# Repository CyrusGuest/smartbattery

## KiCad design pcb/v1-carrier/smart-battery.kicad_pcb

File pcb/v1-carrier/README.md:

# Smart Battery PCB

KiCad project for the Smart Battery carrier PCB. The board is a **carrier** that off-the-shelf modules plug into via pin headers — no bare ICs in v1.

> **Source of truth for connections**: `firmware/HARDWARE.md` in the repo root. Anything here that contradicts that file is wrong; HARDWARE.md wins.

## First-time KiCad setup

1. **Open KiCad** (`/Applications/KiCad/KiCad.app`).
2. KiCad will ask whether to import settings from a previous version — pick **"Start with default settings"**.
3. KiCad will ask about library paths — accept the defaults.
4. **File → New Project…** → navigate to `~/programming/smart-battery/pcb/` → name it `smart-battery` → uncheck "Create a new folder" (we already have one) → save.
5. You should now see `smart-battery.kicad_pro` and `smart-battery.kicad_sch` in this directory.

That's it for setup. Now we draw the schematic.

## Schematic plan

This translates `firmware/HARDWARE.md` into KiCad symbols and nets. **Read HARDWARE.md first** to understand the topology — especially the INA219 in-line-with-cell+ wiring.

### Symbols to place

You won't find ready-made symbols for module breakouts in KiCad's stock library. For a carrier PCB, the right move is to use generic **pin header** symbols (`Connector_Generic:Conn_01x06`, etc.) and label them with the module name.

| Symbol                       | Module it represents                | Pin count | KiCad symbol                        |
| ---------------------------- | ----------------------------------- | --------- | ----------------------------------- |
| **U1 — ESP32**               | ESP32 dev board (whichever you have) | varies (15, 19, or 20 per side) | `Connector_Generic:Conn_02x15_Odd_Even` (or matching count) |
| **U2 — INA219 breakout**     | Adafruit/clone INA219               | 6         | `Connector_Generic:Conn_01x06`      |
| **U3 — TP4056 USB-C charger**| TP4056 module                       | 4–6 (varies) | `Connector_Generic:Conn_01x05` or `01x06` depending on module |
| **U4 — SSD1306 OLED (SPI)**  | 128×64 SPI OLED                     | 7         | `Connector_Generic:Conn_01x07`      |
| **U5 — MOSFET**              | Logic-level N-channel               | 3 (G/D/S) | `Device:Q_NMOS_GSD` (real symbol, not header) |
| **SW1 — Fire switch**        | Momentary, normally-open            | 2         | `Switch:SW_Push`                    |
| **J1 — Coil connector**      | Whatever you pick (510 thread / pads / connector) | 2 | `Connector_Generic:Conn_01x02` |
| **BT1 — LiPo cell**          | Single cell via JST-PH              | 2         | `Connector:Conn_01x02_Pin` (label as JST-PH) |

> Why headers? Because in v1 you're soldering pin headers onto each module and onto the carrier PCB. The "symbol" is just the row of holes the module plugs into. Footprint matches.

### Nets (connections)

Pulled straight from `firmware/HARDWARE.md`. **Power topology is critical** — the INA219 sits in series with the cell+, so loads connect to V−, NOT V+.

**Power rail (the high-current path)**

```
BT1 (cell)   ─[+]─▶ U2.V+ (INA219)
                    │
                    [internal shunt]
                    │
                   U2.V- ──┬──▶ U3.OUT+ (TP4056 BAT+ side, charger output to "system")
                            ├──▶ U1.VIN  (ESP32 dev board VIN)
                            ├──▶ U5.D    (MOSFET drain)
                            └──▶ J1.1    (coil + terminal — the OTHER side goes to U5.S)

BT1 (cell)   ─[−]─▶ GND  ───┬── U2.GND, U3.GND, U1.GND, J1.2, etc.
U3 USB-C input ─── (handled internally by the TP4056 module)
```

Then `U5.G` (MOSFET gate) is driven by `U1.GPIO27`, and `U5.S` (source) returns to GND through the coil. So the coil is between **V−rail** and the **MOSFET drain**, with the source on GND. (Standard low-side switch.)

**3.3 V rail (logic)**

```
U1 (ESP32) 3V3 pin ──┬── U2.Vcc (INA219 logic supply, 3.3V — NOT cell rail)
                      └── U4.VCC (OLED)
```

**I²C (INA219)**

```
U1.GPIO21 ── U2.SDA
U1.GPIO22 ── U2.SCL
```

(Optional but recommended: 4.7 kΩ pull-ups from SDA → 3V3 and SCL → 3V3. The Adafruit INA219 breakout already has them — if you're using one, skip.)

**SPI (OLED)**

```
U1.GPIO5  ── U4.CS
U1.GPIO17 ── U4.DC
U1.GPIO16 ── U4.RST
U1.GPIO23 ── U4.MOSI  (labelled "D1" or "SDA" on some OLED boards)
U1.GPIO18 ── U4.CLK   (labelled "D0" or "SCL" on some OLED boards)
```

**Fire switch**

```
U1.GPIO4 ── SW1.1
SW1.2 ──── GND
```

(Internal pull-up on GPIO 4 is enabled in firmware — no external resistor needed.)

**MOSFET gate**

```
U1.GPIO27 ──[Rg, ~220 Ω]── U5.G
                            │
                           [Rgs, 100 kΩ to GND]   <-- pull-down so the gate is OFF
                            │                          before ESP32 boots / on reset
                            ▼
                           GND
```

This is belt-and-suspenders with the firmware's `digitalWrite(27, LOW)` first thing in `setup()`. The pull-down keeps the MOSFET off during the few ms before the ESP32 even reaches `setup()`.

## Workflow checklist

Each step has a finish line — when you can check the box, move on.

- [ ] **Project created** — `pcb/smart-battery.kicad_pro` exists.
- [ ] **Schematic drawn** — open `smart-battery.kicad_sch`, place all symbols above, wire them per the nets above. Use net labels (the green `<` arrow tool) for power rails (`+BATT_V+`, `+SYS`, `+3V3`, `GND`) — they're cleaner than running long wires.
- [ ] **ERC pass** — Inspect → Electrical Rules Checker → Run. Should be 0 errors. (Warnings about no-connect on unused header pins are fine.)
- [ ] **Footprints assigned** — Tools → Assign Footprints. For headers use `Connector_PinHeader_2.54mm:PinHeader_1x{N}_P2.54mm_Vertical`. For the MOSFET, pick `Package_TO_SOT_SMD:SOT-23` (assuming surface-mount) or `Package_TO_SOT_THT:TO-220-3_Vertical` (through-hole).
- [ ] **PCB layout** — File → Switch to PCB Editor. Update from schematic (the green ↓ arrow). Place modules. Route. Run DRC.
- [ ] **Manufacturing files** — once happy, File → Fabrication Outputs → Gerbers (and drill files). Send to JLCPCB / PCBWay / OSH Park.

## Tips for first-time PCB layout

- **Set a board outline first** before placing parts. Edit the `Edge.Cuts` layer with a rectangle (your Geekbar form factor — see chat with Claude for current target dimensions).
- **Place mechanical parts first**: USB-C jack on one short edge, fire switch on a long edge, OLED in the center, coil connector on the opposite short edge.
- **Power traces wider than signal**: 1.0–2.0 mm for the cell/coil rail (carries amps), 0.25 mm is fine for I²C / SPI / GPIO.
- **Keep INA219 close to the cell connector** — its sense path is part of the high-current loop, and any wire between the cell and INA V+ is shunt resistance you didn't measure.
- **DRC must be clean** before exporting gerbers. Always.

## When you're stuck

`HARDWARE.md` and this README cover *what* to wire. If KiCad UI is the question, check:

- KiCad's built-in "Getting Started in KiCad" tutorial: Help → Getting Started.
- Digi-Key's KiCad video series on YouTube — short, current, and free.
- Or just ask Claude — paste the saved `.kicad_sch` / `.kicad_pcb` content (they're plain-text S-expressions) and I can read and suggest changes.

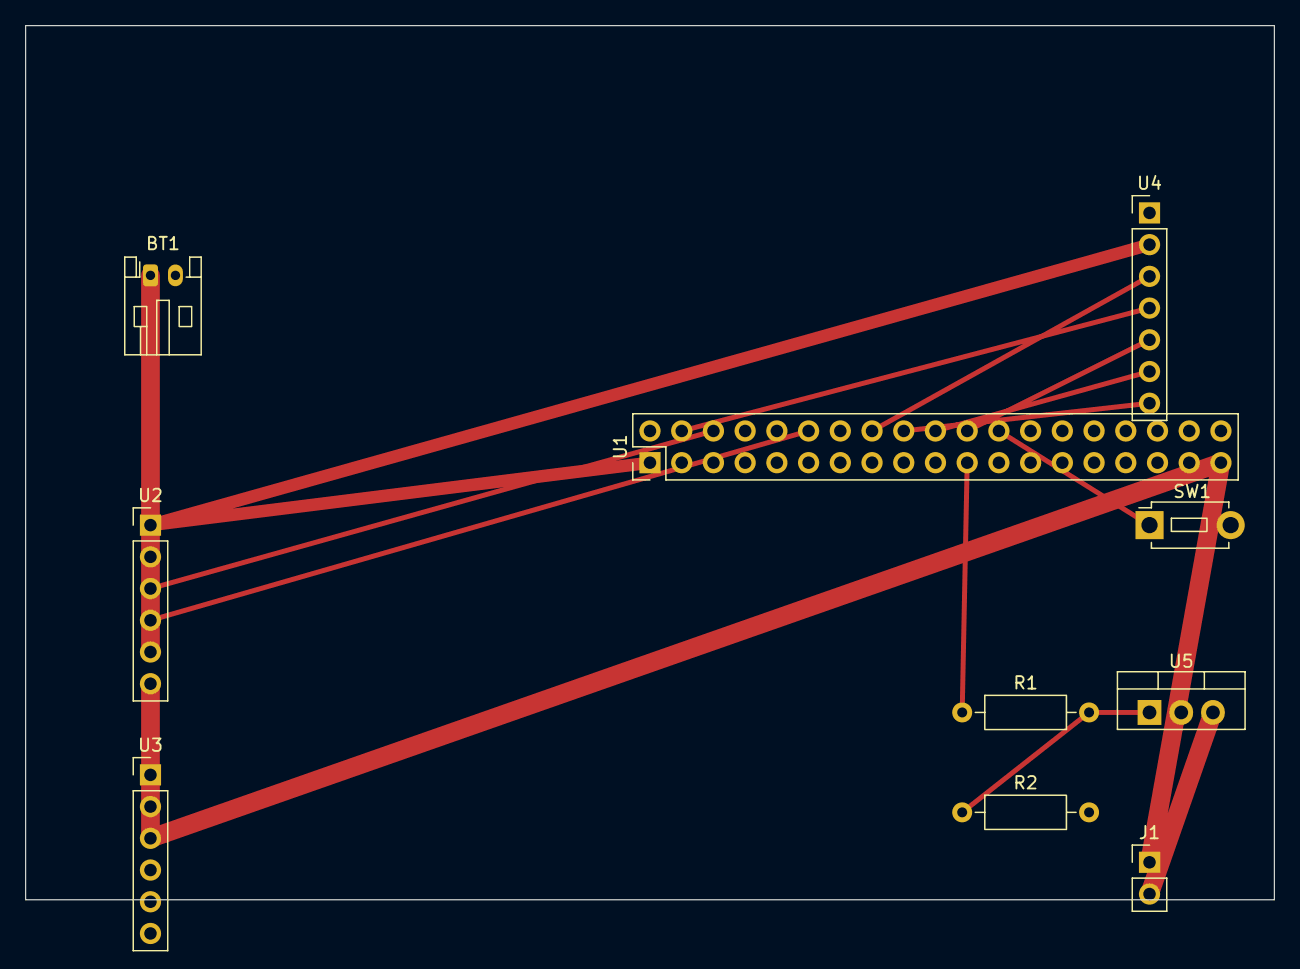
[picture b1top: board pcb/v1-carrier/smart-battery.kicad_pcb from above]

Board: 2 copper layers, 100.0 x 70.0 mm, 10 parts (0 on the bottom side), 15 nets.

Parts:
BT1: LiPo 1S; JST_PH_S2B-PH-K_1x02_P2.00mm_Horizontal
J1: Coil; PinHeader_1x02_P2.54mm_Vertical
R1: 220; R_Axial_DIN0207_L6.3mm_D2.5mm_P10.16mm_Horizontal
R2: 100k; R_Axial_DIN0207_L6.3mm_D2.5mm_P10.16mm_Horizontal
SW1: Fire; SW_PUSH_1P1T_6x3.5mm_H4.3_APEM_MJTP1243
U1: ESP32 38-pin; PinHeader_2x19_P2.54mm_Vertical
U2: INA219; PinHeader_1x06_P2.54mm_Vertical
U3: TP4056; PinHeader_1x06_P2.54mm_Vertical
U4: OLED; PinHeader_1x07_P2.54mm_Vertical
U5: N-MOSFET; TO-220-3_Vertical

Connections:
+3V3: U1.1, U2.1, U4.2
+CELL: BT1.1, U2.5
+SYS: J1.1, U1.37, U2.6, U3.1, U3.3
COIL_GATE: R1.2, R2.1, U5.1
COIL_LOW: J1.2, U5.3
COIL_PWM: R1.1, U1.21
GND: BT1.2, R2.2, SW1.2, U1.2, U1.27, U1.38, U2.2, U3.2, U3.4, U4.1, U5.2
OLED_CLK: U1.16, U4.3
OLED_CS: U1.18, U4.7
OLED_DC: U1.20, U4.6
OLED_MOSI: U1.4, U4.4
OLED_RST: U1.22, U4.5
SCL: U1.6, U2.3
SDA: U1.12, U2.4
SWITCH: SW1.1, U1.24

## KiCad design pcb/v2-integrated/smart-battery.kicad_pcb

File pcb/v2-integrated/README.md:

# Smart Battery PCB — v2 (Integrated SMD)

Production-target board: fully integrated SMD design, JLCPCB PCBA-assembled, no plug-in modules. Replaces the v1 carrier prototype at `../v1-carrier/`.

## Goals

- **Compact**: target ≤ 30 × 80 mm, fits in a Geekbar-style enclosure alongside a 1S LiPo pouch
- **Mass-producible**: every part on JLCPCB's Basic or Extended catalog, all SMD, single-side population where feasible
- **No hand-soldering**: end user receives an assembled PCBA from JLCPCB
- **USB-C flashing & charging**: single port for both, no extra programmer needed
- **Looks like a real product**: tasteful PCB silkscreen, components arranged so the housing can be a clean rectangular envelope

## Block diagram

```
USB-C ──┬──► TP4056 (charger) ──► P+ ─┬──► INA219.V- (= +SYS)
        │                             │
        │     CC1/CC2 = 5.1k pdwn     │
        ▼                             │
       ESD                            │
        │                             │
        ▼                             │
  ESP32-S3 D+/D-                      │
                                      │
Cell+ ──► INA219.V+ ──[shunt 0.1Ω]──┘
Cell− ──► FS8205A ──► (DW01A controls) ──► system GND

+SYS ──► TPS63031DSK ──► +3V3 ──► ESP32-S3, INA219_logic, OLED

ESP32-S3:
  GPIO 6  ──► R(220) ──► AO3400A gate ──┐
                          │              │
  GPIO 4 ◄── fire switch  ▼              ▼
  GPIO 5/11/16/17/18  → OLED SPI    drain ──► coil ──► J4 (510 thread)
  GPIO 8/9  → I²C ── INA219          source ─► GND     +SYS ──► coil top
  GPIO 19/20 → USB D-/D+ (native)    SS34 flyback drain↔+SYS
```

## BOM (target parts)

| Ref      | Part                     | Package        | LCSC?  | Notes |
|----------|--------------------------|----------------|--------|-------|
| U1       | ESP32-S3-MINI-1-N4       | LGA-65 module  | basic  | 4 MB flash, no PSRAM, PCB antenna |
| U2       | TP4056-42-ESOP8          | ESOP-8         | basic  | 1 A charger; PROG = 1.2 kΩ |
| U3       | DW01A                    | SOT-23-6       | basic  | Cell over-discharge / over-charge / over-current control |
| U4       | FS8205A                  | SOT-23-6       | basic  | Dual N-MOSFET for protection |
| U5       | INA219AIDR               | SOIC-8         | basic  | Bus voltage + current sense, addr 0x40 |
| U6       | TPS63031DSK              | SON-10         | extended | Buck-boost, fixed 3.3 V, ≤500 mA |
| Q1       | AO3400A                  | SOT-23         | basic  | Coil-drive N-MOSFET |
| D1       | SS34                     | SMA            | basic  | Flyback Schottky |
| D2       | USBLC6-2SC6              | SOT-23-6       | basic  | USB ESD protection |
| LED1,2   | 0603 LED green / red     | 0603           | basic  | Charge / standby indicators |
| L1       | 1.5 µH 2.2A              | 1210           | basic  | TPS63031 inductor |
| Rshunt   | 0.1 Ω 1% 1 W             | 2512           | basic  | INA219 sense (matches firmware calibration) |
| R1, R2   | 5.1 kΩ                   | 0603           | basic  | USB-C CC pull-downs (USB2-only sink) |
| Rprog    | 1.2 kΩ                   | 0603           | basic  | TP4056 charge current → 1 A |
| R_LED1,2 | 1 kΩ                     | 0603           | basic  | LED current limit |
| Rg       | 220 Ω                    | 0603           | basic  | MOSFET gate series |
| Rgs      | 100 kΩ                   | 0603           | basic  | MOSFET gate-source pull-down |
| Rsda,scl | 4.7 kΩ                   | 0603           | basic  | I²C pull-ups |
| Ren      | 10 kΩ                    | 0603           | basic  | ESP32 EN pull-up |
| C_in,out | 10 µF / 22 µF MLCC       | 0603 / 0805    | basic  | Bulk decoupling |
| C_byp    | 0.1 µF MLCC              | 0402 / 0603    | basic  | Per-IC bypass |
| J1       | USB-C receptacle 16-pin  | TYPE-C-31-M-12 | basic  | USB 2.0 only, no SuperSpeed |
| J2       | OLED daughterboard       | castellated 1×7 | n/a   | 0.96″ SSD1306 SPI castellated module |
| J3       | JST-PH 1×2               | 2.0 mm pitch   | basic  | Cell connection |
| J4       | 1×2 placeholder          | 2.54 mm THT    | n/a    | 510 thread mechanical TBD |
| SW1      | SMD tactile 6×6 mm       | TS-1187        | basic  | Fire button |

## Power topology

INA219 is in series with **cell+** so all charge and discharge current flows through the 0.1 Ω shunt. The protection MOSFETs (FS8205A, controlled by DW01A) sit in the cell– path. This matches v1 topology — the firmware's calibration (`setCalibration_16V_400mA`) and charging detection (`shuntMv < −5 mV`) are unchanged.

```
Cell+ ──► INA219.V+ ──[shunt]──► INA219.V- ──┬──► TP4056.BAT
                                             ├──► TPS63031.VINA/B
                                             └──► AO3400A drain (via coil)

Cell− ──► FS8205A.B+ ──[FET pair]──► FS8205A.M- ──► system GND
DW01A senses Vcell and over-current, gates FS8205A
```

### Coil-drive sizing

The output stage (AO3400A SOT-23 MOSFET + SS34 SMA Schottky flyback) is sized for **standard 510-thread cannabis cartridges (1.0–2.5 Ω)**, the typical MMJ use case. Worst-case is a 1.0 Ω cart at full charge (4.2 V) drawing ~4.2 A peak — well within the AO3400A's 5.8 A continuous rating and the SS34's 40 A peak rating, with comfortable thermal margin in SOT-23 at typical PWM duty cycles.

**Not suitable for sub-ohm coils** (< 1.0 Ω, e.g. nicotine cloud-chasing setups). Sub-ohm operation would pull 8–28 A through the FET, exceeding the AO3400A's continuous rating. To support that, swap Q1 to an SO-8 part (e.g. SiSF20DN, 60 A / 4 mΩ) and bump D1 to a 5–10 A Schottky.

## Firmware port (ESP32-S3)

The firmware needs a small pin remap because S3 silicon doesn't have GPIOs 22/23/27:

```c
// firmware/smartbattery.ino
#define PIN_FIRE     4   // unchanged
#define PIN_OLED_CS  5   // unchanged
#define PIN_OLED_RST 16  // unchanged
#define PIN_OLED_DC  17  // unchanged
#define PIN_OLED_CLK 18  // unchanged
#define PIN_I2C_SDA  8   // was 21
#define PIN_I2C_SCL  9   // was 22
#define PIN_OLED_MOSI 11 // was 23
#define PIN_COIL_PWM 6   // was 27
```

USB CDC is native; flashing works over USB-C with `esptool.py` or Arduino IDE without an external programmer. EN/IO0 are managed by the chip's USB-Serial/JTAG controller — no auto-reset transistors required on the board.

## Layout intent (TBD — to be drawn after schematic)

- **4-layer stackup**: Sig / GND / +3V3 / Sig — gives clean ground reference for ESP32 antenna and INA219 sense pair
- ESP32-S3-MINI-1 placed at one short edge with **antenna corner copper-free** (no traces, no pour, including bottom layer)
- USB-C connector co-located with ESP32 (short native-USB traces, ESD diodes right at the port)
- TP4056 + protection circuit clustered near JST-PH cell connector to keep high-current paths short
- INA219 hugs the shunt resistor; both close to cell+ side
- Coil MOSFET + flyback diode close to coil connector (fast switching loop)
- OLED daughterboard slot opposite the USB-C edge so the screen faces "up" out of the housing
- Fire button on a long edge

## Status

- [x] v1 carrier archived to `../v1-carrier/`
- [x] v2 schematic drafted (42 components + 4 power flags = 46 instances, 38 nets, 31 NC markers)
- [x] ERC clean (0 errors, 73 cosmetic warnings)
- [x] Footprints assigned (all SMD — see BOM table; 6 THT items: J2 OLED daughterboard pins, J3 cell, J4 coil, J5 debug pads, plus mechanical mounting)
- [x] Initial PCB layout: 30×85 mm rounded-rectangle, 42 footprints placed in functional clusters, 15 critical traces routed, B.Cu GND pour
- [x] First pass programmatic cleanup (LED + EN-cluster spread, U2 footprint TODO)
- [x] **Full re-layout + autoroute (2026-09-10, via KiCad IPC API): DRC clean — 0 errors, 0 warnings, 0 unrouted.**
  - Placement fixes: J1 USB-C was rotated 180° (pads were hanging off-board!), SW1 rotated 90°, J5 rotated horizontal (extended 7 mm past board edge), J3 cluster/C2/passives spread to kill all courtyard overlaps.
  - Complete rip-up & reroute: all nets routed fresh (grid A* + hand-designed corridors for the USB-C fan-out, TPS63031 SON-10 escape, and TP4056 region). GND via B.Cu plane + per-pad stitching vias; zone islands bridged.
  - `smart-battery.kicad_dru` added: 0.15 mm clearance rules for fine-pitch parts (U6 SON-10 0.4 mm pitch requires this; also J1/D2/U2).
  - Board rules: `min_copper_edge_clearance` 0.5 → 0.15 (J3 side-entry JST overhangs by design); lib_footprint_mismatch + silk_edge_clearance severities set to ignore (footprints intentionally edited; connector silk clipped at edge is cosmetic).
  - Reference designators hidden on passives (R/C/L/LED/D/Q) to clear silk overlaps.
  - NOTE: still 2-layer (F.Cu signals / B.Cu GND plane). The 4-layer stackup + U1 antenna keep-out from the wishlist below are NOT yet done.

### Remaining DRC errors (for KiCad UI work)

| Count | Type | What to do |
|---|---|---|
| 29 | solder_mask_bridge | Tighten mask design rules (Board Setup → Solder Mask/Paste → reduce mask expansion to 0.05mm), and/or spread close pads |
| 12 | shorting_items | Reroute the few traces that pass too close to other-net pads. Most offenders are around U2 (TP4056) where 1.27mm pitch + 0.5–0.8mm trace doesn't leave clearance. Drop trace width to 0.25mm in that area. |
| 11 | courtyards_overlap | Spread tightly-packed 0603 components by another 0.5mm |
| 8 | copper_edge_clearance | Re-fill GND pour 0.5mm inside board outline (delete current pour, re-add 1mm in) |
| 6 | drill_out_of_range | **Replace U2 footprint** from `HSOP-8-1EP_…_ThermalVias` to `HSOP-8-1EP_…` (no thermal vias) — Edit Footprint Properties → swap library variant |
| 5 | clearance | Same as shorting — narrow traces near TP4056 |
| 2 | tracks_crossing | Reroute one of the two crossing traces on B.Cu |
| 1 | copper_sliver | Refill zones (`B`) |

Cosmetic warnings (45): silk overlap, silk over copper, silk off-edge — set Reference text size = 0 on small SMD parts (or "hide reference" property).
- [ ] Custom symbols for DW01A and FS8205A (currently `Conn_01x06` placeholders) — replace with proper SOT-23-6 schematic symbols
- [ ] 4-layer stackup (signals/GND/3V3/signals) — set in KiCad UI: File → Board Setup → Board Stackup
- [ ] Antenna keep-out zone around U1 (top edge 6×7 mm clear of copper on all layers)
- [ ] DRC clean
- [ ] Firmware pin remap pushed (4 `#define` changes)
- [ ] Schematic PDF + BOM CSV exports for review
- [ ] First assembly order placed at JLCPCB

## Pre-order status (2026-09-20)

Automated session results:
- [x] 4× M2 (2.2 mm NPTH) mounting holes at (52.5,131), (70.5,129), (52.5,103), (75.5,66.5) — Edge.Cuts circles with GND-plane pull-backs (screw-head safe). Verify against enclosure bosses before ordering.
- [x] Antenna keep-out done; SCL/USB/I2C rerouted around it; DRC 0 errors.
- [x] Fab outputs generated in `fab/`: gerbers + drill, `smart-battery-cpl.csv` (JLC placement), `smart-battery-bom.csv` (LCSC numbers — J2/J4 have none: J2 OLED module hand-soldered, J4 mechanical TBD).
- [x] **Final 2 ratsnest lines hand-routed in GUI (2026-09-21). DRC: 0 errors / 0 warnings / 0 unconnected.** Fab outputs in `fab/` regenerated from the final board: `smart-battery-gerbers.zip` (gerbers+drill), `smart-battery-cpl.csv`, `smart-battery-bom.csv`. Board is order-ready pending JLCPCB upload checks (viewer + rotations).
- Note: `starved_thermal` severity set to *ignore* in the project (J2.1's plane spokes are choked by the corridor; if you want it strict, give J2.1 a direct via strap after the cleanup).

## Schematic notes

- **DW01A and FS8205A** are placed as `Connector_Generic:Conn_01x06` placeholders. Pin assignments used:
  - DW01A: 1=OD, 2=CS/VM, 3=TD (NC), 4=OC, 5=VSS, 6=VDD
  - FS8205A: 1=G1, 2=S1 (BAT−), 3=D (NC), 4=D (NC), 5=G2, 6=S2 (PACK−=GND)
  - When swapping to proper symbols/footprints, verify pin numbering matches the actual datasheet (variant-dependent).
- **PWR_FLAG** symbols on VBUS, +CELL, BAT_NEG, GND rails to satisfy ERC's "power input pin not driven" check. +SYS and +3V3 don't need flags because TP4056.BAT and TPS63031.VOUT are already declared as power_output pins.
- **TPS63031 FB pin** tied to +3V3 (= VOUT). Per TI app note, the fixed-output variant has FB internally connected; tying externally to VOUT is the recommended best practice for stability.
- **Castellated OLED daughterboard** uses `Conn_01x07` symbol; expects the standard SSD1306 SPI pinout: 1=GND, 2=VCC, 3=CLK, 4=MOSI, 5=RST, 6=DC, 7=CS. Source any ~0.96″ castellated module that matches.
- **DEBUG header (J5)** is a 5-pin test pad row (TXD0, RXD0, IO0, EN, GND) — not a populated connector, just labeled pads on the silk for factory/dev recovery if USB-Serial/JTAG ever hangs.

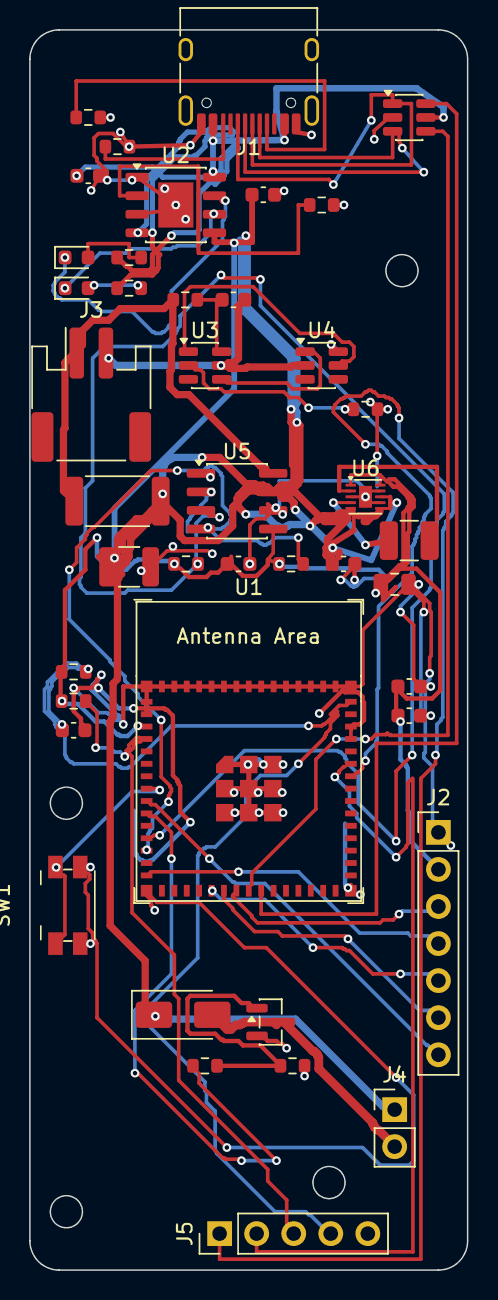
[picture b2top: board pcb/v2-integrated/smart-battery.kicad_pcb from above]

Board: 2 copper layers, 30.0 x 85.0 mm, 42 parts (0 on the bottom side), 38 nets.

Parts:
C1, C2, C5, C7: 10uF; C_0603_1608Metric
C3, C4, C8: 0.1uF; C_0603_1608Metric
C6: 22uF; C_0805_2012Metric
C9: 1uF; C_0603_1608Metric
C10: 100uF; C_1210_3225Metric
D1: SS34; D_SMA
D2: USBLC6-2SC6; SOT-23-6
J1: USB-C; USB_C_Receptacle_HRO_TYPE-C-31-M-12
J2: OLED; PinHeader_1x07_P2.54mm_Vertical
J3: LiPo 1S; JST_PH_S2B-PH-SM4-TB_1x02-1MP_P2.00mm_Horizontal
J4: Coil 510; PinHeader_1x02_P2.54mm_Vertical
J5: DEBUG; PinHeader_1x05_P2.54mm_Vertical
L1: 1.5uH; L_1210_3225Metric
LED1: CHRG (red); LED_0603_1608Metric
LED2: STDBY (green); LED_0603_1608Metric
Q1: AO3400A; SOT-23
R1, R2: 5.1k; R_0603_1608Metric
R3: 1.2k; R_0603_1608Metric
R4, R5, R7: 1k; R_0603_1608Metric
R6: 100; R_0603_1608Metric
R8: 0.1 1W; R_2512_6332Metric
R9, R10: 4.7k; R_0603_1608Metric
R11, R12: 10k; R_0603_1608Metric
R13: 220; R_0603_1608Metric
R14: 100k; R_0603_1608Metric
SW1: Fire; Panasonic_EVQPUJ_EVQPUA
U1: ESP32-S3-MINI-1-N4; ESP32-S3-MINI-1
U2: TP4056; HSOP-8-1EP_3.9x4.9mm_P1.27mm_EP2.41x3.1mm
U3: DW01A; SOT-23-6
U4: FS8205A; SOT-23-6
U5: INA219; SOIC-8_3.9x4.9mm_P1.27mm
U6: TPS63031; Texas_DSQ0010A_WSON-10-1EP_2x2mm_P0.4mm_EP0.9x1.5mm

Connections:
+3V3: C4.1, C6.1, C7.1, C8.1, J2.2, R9.1, R10.1, R11.1, R12.1, U1.3, U5.5, U6.1, U6.10
+CELL: J3.1, R6.1, R8.1, U5.8
+SYS: C2.1, C5.1, C10.1, D1.1, J4.1, R8.2, U2.5, U5.7, U6.5, U6.6, U6.8
BAT_NEG: C3.2, J3.2, U3.5, U4.2
CC1: J1.A5, R1.1
CC2: J1.B5, R2.1
CHRG: LED1.1, U2.7
CHRG_LED: LED1.2, R4.2
COIL_GATE: Q1.1, R13.2, R14.1
COIL_LOW: D1.2, J4.2, Q1.3
COIL_PWM: R13.1, U1.10
DW01_OC: U3.4, U4.1
DW01_OD: U3.1, U4.5
DW01_VDD: C3.1, R6.2, U3.6
DW01_VM: R7.1, U3.2
ESP_EN: C9.1, J5.4, R11.2, U1.45
ESP_IO0: J5.3, R12.2, U1.4
GND: C1.2, C2.2, C4.2, C5.2, C6.2, C7.2, C8.2, C9.2, C10.2, D2.2, J1.A1, J1.A12, J1.B1, J1.B12, J2.1, J5.5, Q1.2, R1.2, R2.2, R3.2, R7.2, R14.2, SW1.2, U1.1, U1.2, U1.42, U1.43, U1.46, U1.47, U1.48, U1.49, U1.50, U1.51, U1.52, U1.53, U1.54, U1.55, U1.56, U1.57, U1.58, U1.59, U1.60, U1.61, U1.62, U1.63, U1.64, U1.65, U2.1, U2.3, U2.9, U4.6, U5.1, U5.2, U5.6, U6.3, U6.7, U6.9, U6.11
OLED_CLK: J2.3, U1.22
OLED_CS: J2.7, U1.9
OLED_DC: J2.6, U1.21
OLED_MOSI: J2.4, U1.15
OLED_RST: J2.5, U1.20
PROG: R3.1, U2.2
RXD0: J5.2, U1.40
SCL: R10.2, U1.13, U5.4
SDA: R9.2, U1.12, U5.3
STDBY: LED2.1, U2.6
STDBY_LED: LED2.2, R5.2
SWITCH: SW1.1, U1.8
SW_L1: L1.1, U6.4
SW_L2: L1.2, U6.2
TXD0: J5.1, U1.39
USB_DN: D2.4, U1.23
USB_DN_RAW: D2.3, J1.A7, J1.B7
USB_DP: D2.6, U1.24
USB_DP_RAW: D2.1, J1.A6, J1.B6
VBUS: C1.1, D2.5, J1.A4, J1.A9, J1.B4, J1.B9, R4.1, R5.1, U2.4, U2.8

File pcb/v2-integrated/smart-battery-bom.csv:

Qty,Refdes(es),Value,PKG_TYPE,MFR_PN,Manufacturer,LCSC,Footprint
4,"C1, C2, C5, C7",10uF,0603,CL10A106KQ8NNNC,Samsung,C19702,Capacitor_SMD:C_0603_1608Metric
3,"C3, C4, C8",0.1uF,0603,CL10B104KB8NNNC,Samsung,C1525,Capacitor_SMD:C_0603_1608Metric
1,C6,22uF,0805,CL21A226MAYNNNE,Samsung,C45783,Capacitor_SMD:C_0805_2012Metric
1,C9,1uF,0603,CL10B105KB8NNNC,Samsung,C15849,Capacitor_SMD:C_0603_1608Metric
1,C10,100uF (bulk),1210,CL32A107MQVNNNE,Samsung,C13585,Capacitor_SMD:C_1210_3225Metric
1,D1,SS34,SMA,SS34,MDD,C8678,Diode_SMD:D_SMA
1,D2,USBLC6-2SC6,SOT-23-6,USBLC6-2SC6,STMicroelectronics,C7519,Package_TO_SOT_SMD:SOT-23-6
1,J1,USB-C,USB-C 16-pin SMD,TYPE-C-31-M-12,HRO,C165948,Connector_USB:USB_C_Receptacle_HRO_TYPE-C-31-M-12
1,J2,OLED 0.96 SPI castellated,Castellated 1x7,OLED-0.96-CASTL-7P,Generic (sourced),,Connector_PinHeader_2.54mm:PinHeader_1x07_P2.54mm_Vertical
1,J3,LiPo 603450 (JST-PH),JST-PH SMD 1x2,S2B-PH-SM4-TB(LF),JST,C265084,Connector_JST:JST_PH_S2B-PH-SM4-TB_1x02-1MP_P2.00mm_Horizontal
1,J4,Coil 510 (TBD),TBD (510 thread),510-CONNECTOR-TBD,TBD,,Connector_PinHeader_2.54mm:PinHeader_1x02_P2.54mm_Vertical
1,J5,DEBUG (TX0/RX0/IO0/EN/GND),Test pads 1x5,TEST-PAD-1x5,n/a,,Connector_PinHeader_2.54mm:PinHeader_1x05_P2.54mm_Vertical
1,L1,1.5uH,1210,MWSA1210SR-1R5MTAH,Sunlord,C133988,Inductor_SMD:L_1210_3225Metric
1,LED1,CHRG (red),0603,KT-0603R,Hubei KENTO,C2286,LED_SMD:LED_0603_1608Metric
1,LED2,STDBY (green),0603,KT-0603G,Hubei KENTO,C2297,LED_SMD:LED_0603_1608Metric
1,Q1,AO3400A,SOT-23,AO3400A,Alpha & Omega,C20917,Package_TO_SOT_SMD:SOT-23
2,"R1, R2",5.1k,0603,RC0603FR-075K1L,Yageo,C23186,Resistor_SMD:R_0603_1608Metric
1,R3,1.2k,0603,RC0603FR-071K2L,Yageo,C22849,Resistor_SMD:R_0603_1608Metric
3,"R4, R5, R7",1k,0603,RC0603FR-071KL,Yageo,C21190,Resistor_SMD:R_0603_1608Metric
1,R6,100,0603,RC0603FR-07100RL,Yageo,C22775,Resistor_SMD:R_0603_1608Metric
1,R8,0.1 2W,2512,PE2512FKE070R1L,Yageo,C84395,Resistor_SMD:R_2512_6332Metric
2,"R9, R10",4.7k,0603,RC0603FR-074K7L,Yageo,C23162,Resistor_SMD:R_0603_1608Metric
2,"R11, R12",10k,0603,RC0603FR-0710KL,Yageo,C25804,Resistor_SMD:R_0603_1608Metric
1,R13,220,0603,RC0603FR-07220RL,Yageo,C22962,Resistor_SMD:R_0603_1608Metric
1,R14,100k,0603,RC0603FR-07100KL,Yageo,C25741,Resistor_SMD:R_0603_1608Metric
1,SW1,Fire,6x6 SMD,EVQ-PUJ02K,Panasonic,C77890,Button_Switch_SMD:Panasonic_EVQPUJ_EVQPUA
1,U1,ESP32-S3-MINI-1-N4,LGA-65,ESP32-S3-MINI-1-N4,Espressif,C2913200,Espressif:ESP32-S3-MINI-1
1,U2,TP4056,ESOP-8,TP4056-42-ESOP8,Nanjing Top Power,C16581,Package_SO:HSOP-8-1EP_3.9x4.9mm_P1.27mm_EP2.41x3.1mm_ThermalVias
1,U3,DW01A (placeholder),SOT-23-6,DW01A,Fortune Semi,C351410,Package_TO_SOT_SMD:SOT-23-6
1,U4,FS8205A (placeholder),SOT-23-6,FS8205A,Fortune Semi,C32254,Package_TO_SOT_SMD:SOT-23-6
1,U5,INA219AIDR,SOIC-8,INA219AIDR,Texas Instruments,C138563,Package_SO:SOIC-8_3.9x4.9mm_P1.27mm
1,U6,TPS63031DSK,WSON-10,TPS63031DSKR,Texas Instruments,C57898,Package_DFN_QFN:Texas_DSQ0010A_WSON-10-1EP_2x2mm_P0.4mm_EP0.9x1.5mm

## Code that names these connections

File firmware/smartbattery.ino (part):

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#define SCREEN_WIDTH  128
#define SCREEN_HEIGHT 64

#define OLED_CS    5
#define OLED_DC    17
#define OLED_RST   16
#define OLED_MOSI  23
#define OLED_CLK   18

#define SWITCH_PIN    4
#define PWM_PIN       27    // PWM output for power control
// INA219 uses I2C on GPIO 21 (SDA) and GPIO 22 (SCL)

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    delay(1000);
    Serial.println("\n=== Smart Battery ===");

    pinMode(SWITCH_PIN, INPUT_PULLUP);

    // Display init
    pinMode(OLED_RST, OUTPUT);
    digitalWrite(OLED_RST, HIGH);
    delay(10);
    digitalWrite(OLED_RST, LOW);
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}

void loop() {
    bool switchOn = (digitalRead(SWITCH_PIN) == LOW);

    // Wake screen on button press
    if (switchOn && lastSwitchState == HIGH) {
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
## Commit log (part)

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2026-01-27 Initial commit
    Generated by create-expo-app 3.5.3.
2026-04-13 Add firmware, update .gitignore, remove swap file
